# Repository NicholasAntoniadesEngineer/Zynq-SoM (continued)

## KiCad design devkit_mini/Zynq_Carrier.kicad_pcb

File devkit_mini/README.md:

<!-- schgen:gallery -->
<!-- GENERATED by `schgen gallery` — edits between these markers are overwritten -->
## Generated 3D board views

The placed board rendered from 8 angles by `schgen board` (kicad-cli, the real component 3D models) — regenerated and committed every build, just like the sheets below.

|   |   |   |   |
|---|---|---|---|
| <br>**Perspective (front)** | <br>**Perspective (rear)** | <br>**Top** | <br>**Bottom** |
| <br>**Front edge** | <br>**Back edge** | <br>**Left edge** | <br>**Right edge** |

## Ratsnest views

Placed-board airwires, regenerated by `schgen board`: blue/orange = the subsystem's parts (top/bottom side), steel = SoM, green = intra-subsystem, red = to the SoM. `wired` = in `placement.wired_sheets`.

|   |   |
|---|---|
| <br>**Board (top)** | <br>**Board (bottom)** |
| <br>**SoM region** |   |

|   |   |   |   |
|---|---|---|---|
| <br>**debug_boot** | <br>**mechanical** | <br>**pd_input** `wired` | <br>**power** `wired` |
| <br>**power_mon** | <br>**power_som** | <br>**uart_bridge** `wired` | <br>**usb_uart_connector** `wired` |

## Generated schematics

Block diagram and all 12 devkit_mini sheets, regenerated by `schgen board` —
every PNG below passed the netlist, ERC and visual gates.

|   |   |   |
|---|---|---|
| <br>**debug_boot** | <br>**mechanical** | <br>**pd_input** |
| <br>**power** | <br>**power_mon** | <br>**power_som** |
| <br>**som_decoupling** | <br>**som_j1** | <br>**som_j2** |
| <br>**som_j3** | <br>**uart_bridge** | <br>**usb_uart_connector** |

| sheet | description |
|---|---|
| [debug_boot](renders/debug_boot.png) | JTAG + SWD headers, boot-request DIP, reset |
| [mechanical](renders/mechanical.png) | Mechanical: M3 mounts + chassis-GND bond (fiducials are PCB-only, emitted by the placer) |
| [pd_input](renders/pd_input.png) | Power inlet: USB-C PD 20V/3A + TPS26631 eFuse |
| [power](renders/power.png) | Power: +VIN->+5V->+3V3 bucks + +1V8 LDO, PG LEDs |
| [power_mon](renders/power_mon.png) | Rail telemetry: 2x INA3221 + shunts (I2C 0x40/41) |
| [power_som](renders/power_som.png) | Power: +VIN -> +5V_SOM always-on buck |
| [som_decoupling](renders/som_decoupling.png) | SoM power-entry decoupling under the DF40 mezzanine |
| [som_j1](renders/som_j1.png) | SoM J1: power / USB / STM32 / JTAG / SDIO / ETH MDI |
| [som_j2](renders/som_j2.png) | SoM J2: FPGA bank 13/33 IO + VCCO rails |
| [som_j3](renders/som_j3.png) | SoM J3: FPGA bank 33/34/35 IO + VCCO rails |
| [uart_bridge](renders/uart_bridge.png) | UART bridge: CP2102N USB-UART |
| [usb_uart_connector](renders/usb_uart_connector.png) | USB-C UFP console port -> CP2102N |
<!-- /schgen:gallery -->

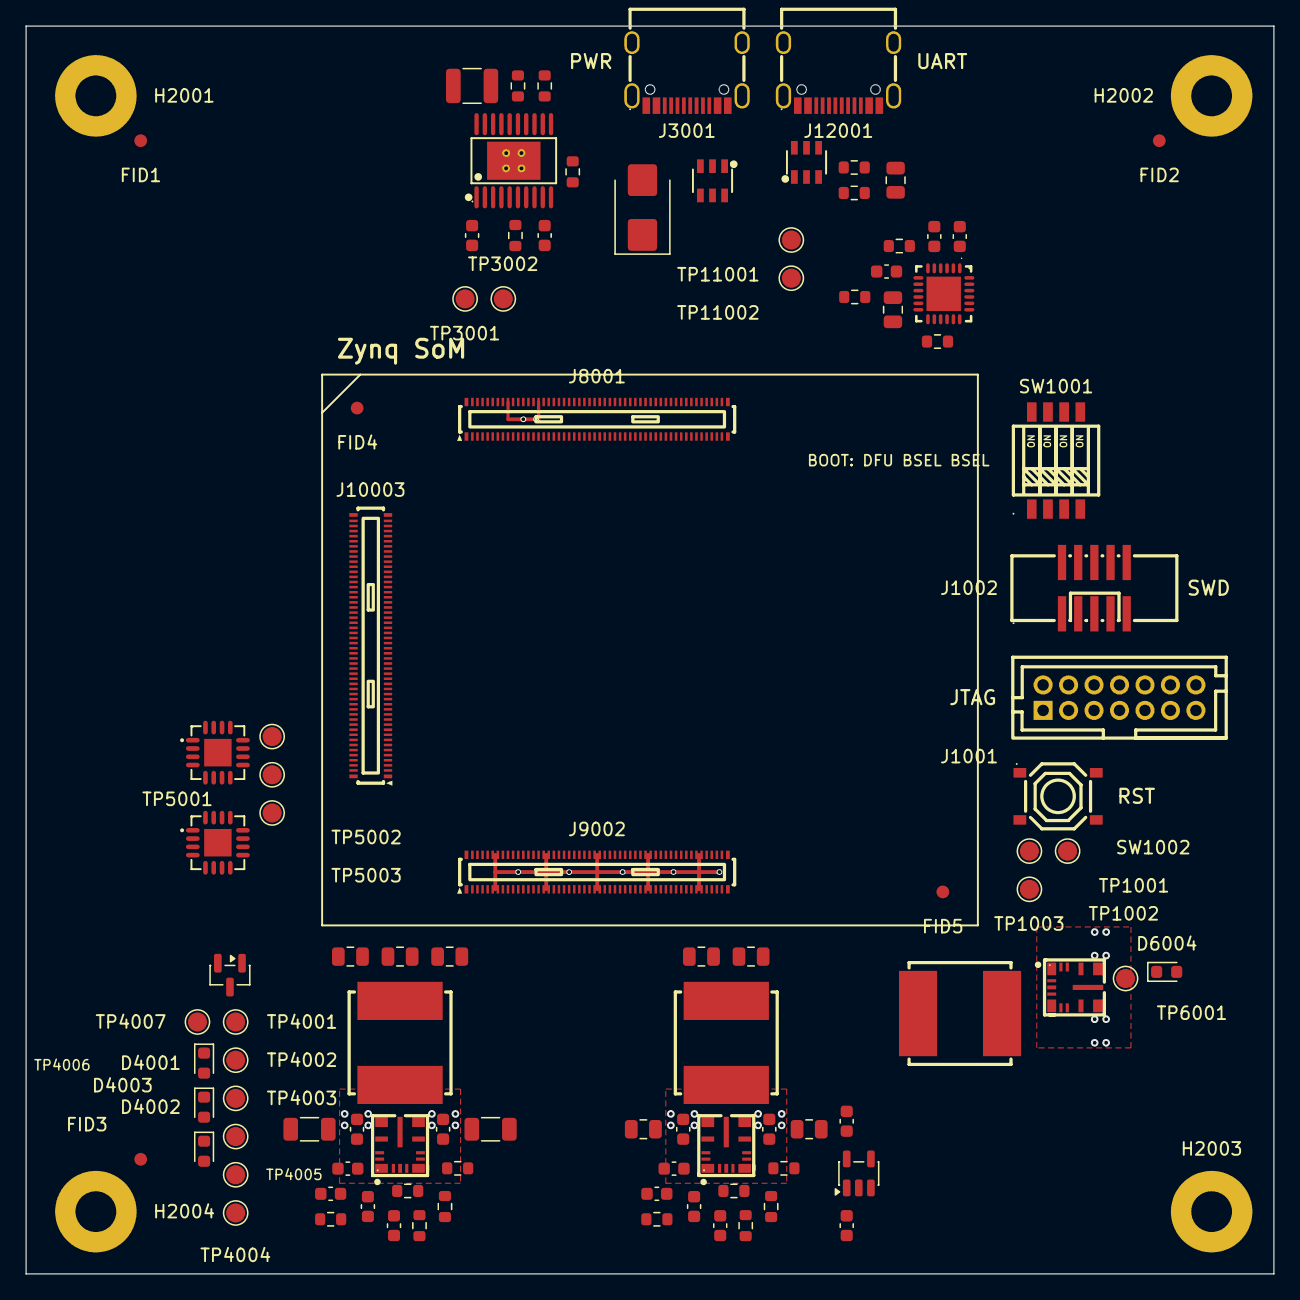
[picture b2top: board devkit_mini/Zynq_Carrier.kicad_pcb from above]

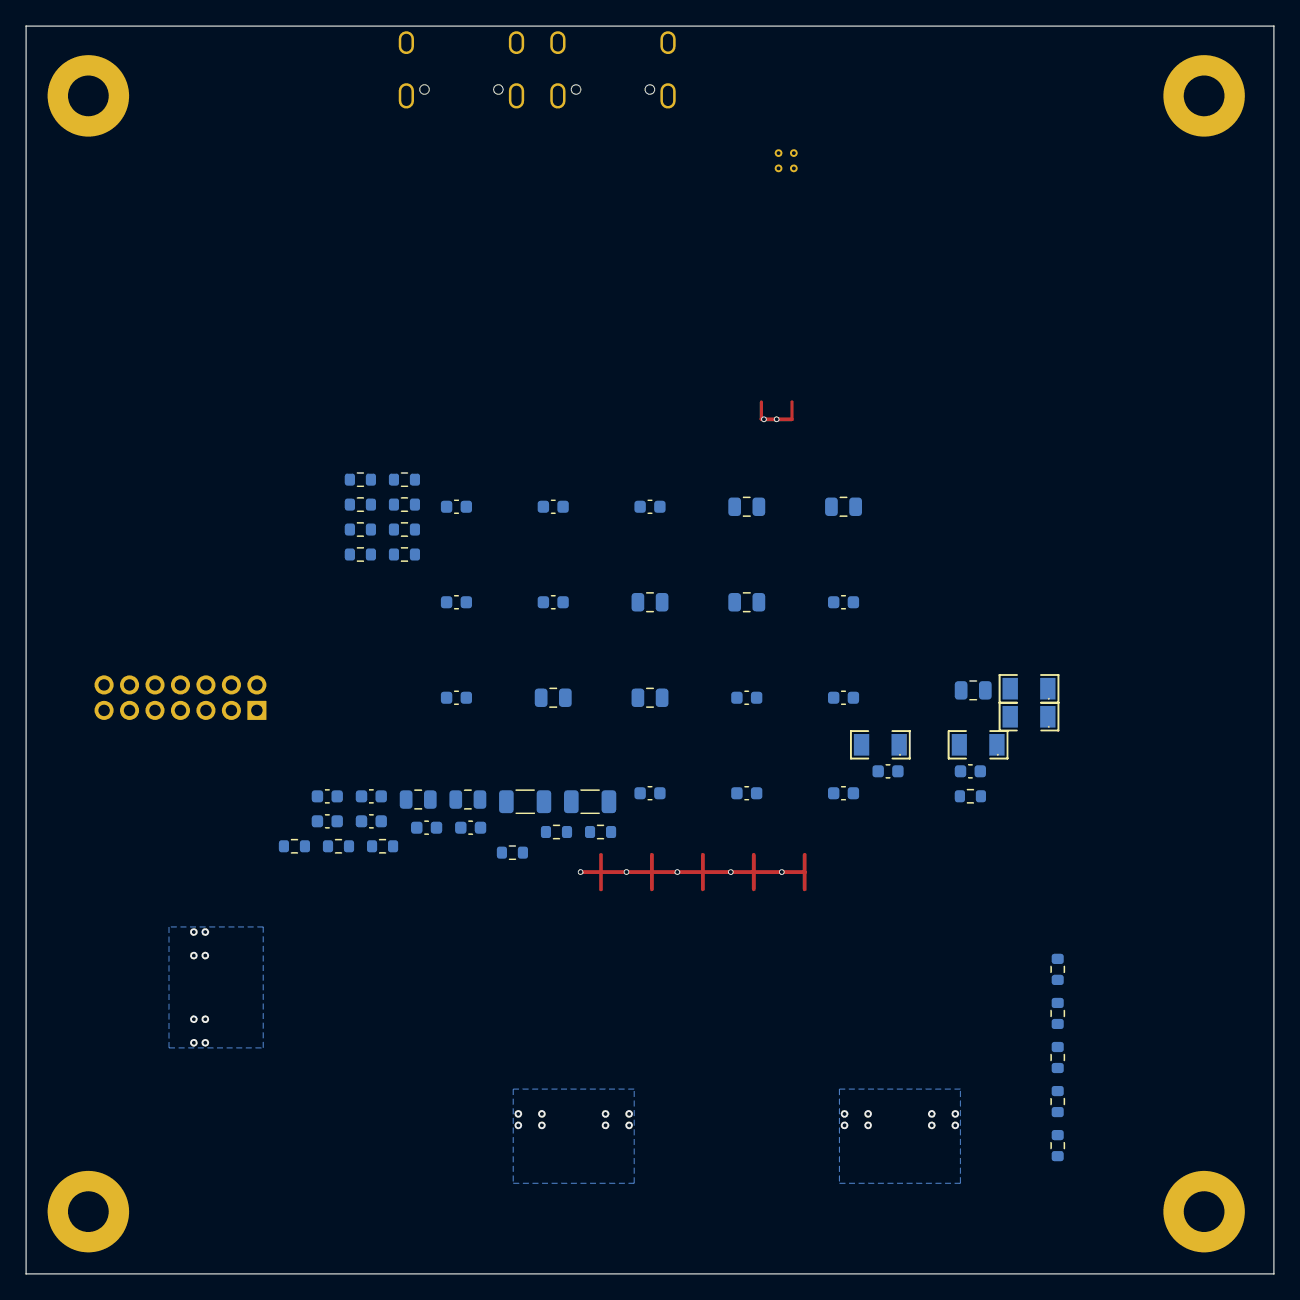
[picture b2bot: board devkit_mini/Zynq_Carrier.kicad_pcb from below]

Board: 4 copper layers, 98.0 x 98.0 mm, 160 parts (55 on the bottom side), 84 nets.

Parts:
C3001, C4001, C4004, C4007, C4009, C4025, C4029, C5001, C5002, C6014, C6017, C6025, C7003, C7004, C7005, C7006, C7009, C7010, C7011, C7012, C7015, C7016, C7017, C7018, C11001, C11003, C11004: 100n; C_0603_1608Metric
C3002: 10u; C_1210_3225Metric
C3003: 47n; C_0603_1608Metric
C4002, C4003, C6015, C6016: 10u; C_1206_3216Metric
C4005, C4006, C4008, C4010, C4011, C4026, C4030, C6018, C6019, C7001, C7002, C7007, C7008, C7013, C7014: 22u; C_0805_2012Metric
C4012, C4013, C4024, C4028, C4031, C4032, C6022, C6023: 1u; C_0603_1608Metric
C4023, C4027, C6021: 22p; C_0603_1608Metric
C5003, C11002, C12001: 10u; C_0805_2012Metric
D3001: SMBJ22A; D_SMB
D4001, D4002, D4003, D6004: red; LED_0603_1608Metric
FID1, FID2, FID3, FID4, FID5: Fiducial; Fiducial_1mm_Mask2mm
H2001, H2002, H2003, H2004: MountingHole_M3; MountingHole_3.2mm_M3_Pad
J1001: 878311420
J1002: HX_JN1.27-2x5; HX_JN1.27-2x5_TP_H4.9
J3001, J12001: TYPE-C-31-M-12
J8001, J9002, J10003: DF40C-100DP-0.4V(51); DF40C-100DP-0.4V_51
L4001, L4002, L6003: 10uH; SWPA8040S100MT
Q4001: AO3400A; SOT-23
R1001, R1002, R1007, R1008: 4k7; R_0603_1608Metric
R1003: 100R; R_0603_1608Metric
R1004, R1005, R1006, R4002, R4005, R5001: 10k; R_0603_1608Metric
R3003, R3006, R4008: 100k; R_0603_1608Metric
R3004: 5.49k; R_0603_1608Metric
R3005, R12001, R12002: 5.1k; R_0603_1608Metric
R4001: 40.2k; R_0603_1608Metric
R4003, R4007, R4012, R4015, R6016, R6019, R11001: 1k; R_0603_1608Metric
R4004: 23.2k; R_0603_1608Metric
R4006, R4009: 330R; R_0603_1608Metric
R4010, R4014, R6018: 22k; R_0603_1608Metric
R4011, R4013, R6017: 10R; R_0603_1608Metric
R6014: 47.5k; R_0603_1608Metric
R6015: 13k; R_0603_1608Metric
R11002: 22k1; R_0603_1608Metric
R11003: 47k5; R_0603_1608Metric
RS5001, RS5002, RS5003: 10mR; RLM12FTCMR010
RS5004: 20mR; RLM12FTCMR020
SW1001: DIP-4; DSHP04TSGER
SW1002: RESET; TS-1187A-B-A-B
TP1001: SDIO_CLK; TestPoint_Pad_D1.5mm
TP1002: SDIO_CMD; TestPoint_Pad_D1.5mm
TP1003: VBUS_OUT_EN; TestPoint_Pad_D1.5mm
TP3001: +VBUS_IN; TestPoint_Pad_D1.5mm
TP3002: +VIN; TestPoint_Pad_D1.5mm
TP4001: +5V; TestPoint_Pad_D1.5mm
TP4002: +3V3; TestPoint_Pad_D1.5mm
TP4003: +1V8; TestPoint_Pad_D1.5mm
TP4004: GND; TestPoint_Pad_D1.5mm
TP4005: EN_5V0; TestPoint_Pad_D1.5mm
TP4006: EN_3V3; TestPoint_Pad_D1.5mm
TP4007: EN_1V8; TestPoint_Pad_D1.5mm
TP5001: +3V3_SC; TestPoint_Pad_D1.5mm
TP5002: STM32_I2C2_SCL; TestPoint_Pad_D1.5mm
TP5003: STM32_I2C2_SDA; TestPoint_Pad_D1.5mm
TP6001: +5V_SOM; TestPoint_Pad_D1.5mm
TP11001: ZYNQ_PS_UART0_TXD; TestPoint_Pad_D1.5mm
TP11002: ZYNQ_PS_UART0_RXD; TestPoint_Pad_D1.5mm
U3001: TPS26631PWPR
U3002, U12001: USBLC6-2SC6
U4001, U4002, U6004: LM61460AANRJRR
U4003: AP2112K-1.8; SOT-23-5
U5001, U5002: INA3221AIRGVR
U11001: CP2102N-A02; CP2102N-A02-GQFN24R

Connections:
+1V8: R4007.1, RS5004.2, TP4003.1, U5002.11
+1V8_REG: C4013.1, RS5004.1, U4003.5, U5002.12
+3V3: C4012.1, C7007.1, C7008.1, C7009.1, C7010.1, C7011.1, C7012.1, C11001.1, C11002.1, C11003.1, C11004.1, D4003.2, J1001.2, J9002.1, J9002.2, J9002.3, J9002.98, J9002.99, J9002.100, J10003.1, J10003.2, J10003.4, J10003.97, J10003.99, R1001.1, R1002.1, R11001.1, RS5003.2, TP4002.1, U4003.1, U5001.1, U11001.5, U11001.6, U11001.7
+3V3_REG: C4010.1, C4011.1, C4023.1, D4002.2, L4002.2, R4004.1, R4013.1, RS5003.1, U5001.2
+3V3_SC: C5001.1, C5002.1, C5003.1, C7013.1, C7014.1, C7015.1, C7016.1, C7017.1, C7018.1, J1002.1, J8001.37, R1003.1, R1004.1, R1005.1, R1006.1, R1007.1, R1008.1, R3006.1, R5001.1, TP5001.1, U3002.5, U5001.4, U5001.16, U5002.4, U5002.5, U5002.16
+5V: C4007.1, C4008.1, C4029.1, C4030.1, RS5002.2, TP4001.1, U4002.8, U4002.12, U5001.14
+5V_REG: C4005.1, C4006.1, C4026.1, C4027.1, D4001.2, L4001.2, R4001.1, R4011.1, RS5002.1, U5001.15
+5V_SOM: C6018.1, C6019.1, C6021.1, C7001.1, C7002.1, C7003.1, C7004.1, C7005.1, C7006.1, D6004.2, J8001.1, J8001.2, J8001.3, J8001.4, J8001.5, J8001.6, J8001.7, J8001.8, J8001.9, J8001.10, J8001.11, J8001.12, J8001.13, J8001.14, L6003.2, R6014.1, R6017.1, TP6001.1
+VBUS_IN: C3001.1, D3001.1, J3001.A4B9, J3001.B4A9, R3003.1, TP3001.1, U3001.1, U3001.2, U3001.3, U3001.6, U3001.7
+VIN: C3002.1, RS5001.1, TP3002.1, U3001.18, U3001.19, U3001.20, U5001.12
+VIN_SYS: C4001.1, C4002.1, C4003.1, C4025.1, C6014.1, C6015.1, C6016.1, C6025.1, RS5001.2, U4001.8, U4001.12, U5001.11, U6004.7, U6004.8, U6004.12
/pd_input/PD_USB_DN_CONN: J3001.A7, J3001.B7, U3002.3
/pd_input/PD_USB_DP_CONN: J3001.A6, J3001.B6, U3002.1
/power/BIAS_3V3: C4032.1, R4013.2, U4002.1
/power/BIAS_5V0: C4028.1, R4011.2, U4001.1
/power/RT_3V3: R4014.1, U4002.6
/power/RT_5V0: R4010.1, U4001.6
/power_som/BIAS_5V_SOM: C6023.1, R6017.2, U6004.1
/power_som/RT_5V_SOM: R6018.1, U6004.6
/uart_bridge/CP2102N_VBUS_SNS: R11002.2, R11003.1, U11001.8
/usb_uart_connector/USB_UART_DM_CONN: J12001.A7, J12001.B7, U12001.3
/usb_uart_connector/USB_UART_DP_CONN: J12001.A6, J12001.B6, U12001.1
CHASSIS_GND: H2001.1, H2002.1, H2003.1, H2004.1, J3001.1, J3001.2, J3001.3, J3001.4, J12001.1, J12001.2, J12001.3, J12001.4
EN_1V8: TP4007.1, U4003.3
EN_3V3: TP4006.1, U4002.7
EN_5V0: TP4005.1, U4001.7
GND: C3001.2, C3002.2, C3003.2, C4001.2, C4002.2, C4003.2, C4005.2, C4006.2, C4007.2, C4008.2, C4010.2, C4011.2, C4012.2, C4013.2, C4024.2, C4025.2, C4026.2, C4028.2, C4029.2, C4030.2, C4031.2, C4032.2, C5001.2, C5002.2, C5003.2, C6014.2, C6015.2, C6016.2, C6018.2, C6019.2, C6022.2, C6023.2, C6025.2, C7001.2, C7002.2, C7003.2, C7004.2, C7005.2, C7006.2, C7007.2, C7008.2, C7009.2, C7010.2, C7011.2, C7012.2, C7013.2, C7014.2, C7015.2, C7016.2, C7017.2, C7018.2, C11001.2, C11002.2, C11003.2, C11004.2, C12001.2, D3001.2, J1001.1, J1001.3, J1001.5, J1001.7, J1001.9, J1001.11, J1001.13, J1002.3, J1002.5, J1002.9, J3001.A1B12, J3001.B1A12, J8001.15, J8001.16, J8001.17, J8001.18, J8001.23, J8001.28, J8001.34, J8001.39, J8001.44, J8001.51, J8001.62, J8001.63, J8001.72, J8001.75, J8001.81, J8001.82, J8001.87, J8001.93, J8001.96, J8001.99, J9002.4, J9002.5, J9002.6, J9002.15, J9002.16, J9002.25, J9002.26, J9002.35, J9002.36, J9002.45, J9002.46, J9002.55, J9002.56, J9002.65, J9002.66, J9002.75, J9002.76, J9002.85, J9002.86, J9002.95, J9002.96, J9002.97, J10003.3, J10003.6, J10003.12, J10003.13, J10003.18, J10003.23, J10003.28, J10003.33, J10003.38, J10003.43, J10003.48, J10003.53, J10003.58, J10003.63, J10003.68, J10003.73, J10003.80, J10003.83, J10003.90, J10003.95, J10003.100, J12001.A1B12, J12001.B1A12, Q4001.2, R3004.2, R3005.2, R4002.2, R4003.2, R4005.2, R4006.2, R4008.2, R4010.2, R4014.2, R6015.2, R6016.2, R6018.2, R11003.2, R12001.2, R12002.2, SW1001.5, SW1001.6, SW1001.7, SW1002.3, SW1002.4, TP4004.1, U3001.9, U3001.12, U3001.16, U3001.21, U3002.2, U4001.3, U4001.9, U4001.11, U4002.3, U4002.9, U4002.11, U4003.2, U5001.3, U5001.5, U5001.17, U5002.1, U5002.2, U5002.3, U5002.14, U5002.15, U5002.17, U6004.3, U6004.9, U6004.11, U11001.2, U11001.25, U12001.2
unnamed: C4023.2, R4015.1
unnamed: C4027.2, R4012.1
unnamed: C6021.2, R6019.1
unnamed: D4001.1, R4003.1
unnamed: D4002.1, R4006.1
unnamed: D4003.1, R4009.1
unnamed: D6004.1, R6016.1
unnamed: J12001.A5, R12001.1
unnamed: J12001.B5, R12002.1
unnamed: Q4001.3, R4009.2
unnamed: Q4001.1, R4007.2, R4008.1
unnamed: R1003.2, SW1001.8
unnamed: R1006.2, SW1001.4
unnamed: R3005.1, U3001.11
unnamed: R3003.2, R3004.1, U3001.8
unnamed: C3003.1, U3001.10
unnamed: C4004.1, U4001.13, U4001.14
unnamed: R4001.2, R4002.1, R4012.2, U4001.4
unnamed: C4004.2, L4001.1, U4001.10
unnamed: C4024.1, U4001.2
unnamed: C4009.1, U4002.13, U4002.14
unnamed: R4004.2, R4005.1, R4015.2, U4002.4
unnamed: C4009.2, L4002.1, U4002.10
unnamed: C4031.1, U4002.2
unnamed: C6017.1, U6004.13, U6004.14
unnamed: R6014.2, R6015.1, R6019.2, U6004.4
unnamed: C6017.2, L6003.1, U6004.10
unnamed: C6022.1, U6004.2
unnamed: R11001.2, U11001.9
PD_FLT_N: R3006.2, U3001.15
PMON_ALERT_N: R5001.2, U5001.9, U5002.9
SDIO_CLK: J8001.67, TP1001.1
SDIO_CMD: J8001.69, TP1002.1
STM32_BOOT0: J8001.57, SW1001.1
STM32_GPIO5: J1002.4, J8001.53
STM32_GPIO6: J1002.2, J8001.45
STM32_GPIO7: J8001.59, R1004.2, SW1001.2
STM32_GPIO8: J8001.54, R1005.2, SW1001.3
STM32_I2C2_SCL: J8001.55, R1007.2, TP5002.1, U5001.6, U5002.6
STM32_I2C2_SDA: J8001.49, R1008.2, TP5003.1, U5001.7, U5002.7
STM32_NRST: J1002.10, J8001.47, SW1002.1, SW1002.2
STM32_USB_CC1: J3001.A5, J8001.29
STM32_USB_CC2: J3001.B5, J8001.31
STM32_USB_D_N: J8001.21, U3002.4
STM32_USB_D_P: J8001.19, U3002.6
USB_UART_DM: U11001.4, U12001.4
USB_UART_DP: U11001.3, U12001.6
USB_UART_VBUS: C12001.1, J12001.A4B9, J12001.B4A9, R11002.1, U12001.5
VBUS_OUT_EN: J8001.38, TP1003.1
ZYNQ_PS_UART0_CTS_N: J9002.11, U11001.19
ZYNQ_PS_UART0_RTS_N: J9002.8, U11001.18
ZYNQ_PS_UART0_RXD: J8001.42, TP11002.1, U11001.21
ZYNQ_PS_UART0_TXD: J8001.48, TP11001.1, U11001.20
ZYNQ_TCK: J1001.6, J8001.64
ZYNQ_TDI: J1001.10, J8001.70, R1002.2
ZYNQ_TDO: J1001.8, J8001.68
ZYNQ_TMS: J1001.4, J8001.66, R1001.2

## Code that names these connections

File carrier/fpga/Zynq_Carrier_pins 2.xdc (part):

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##############################################################################

# ---- bank 13 — VCCO = +3V3 (43 pins) --------------------
set_property -dict {PACKAGE_PIN AA9  IOSTANDARD LVCMOS33} [get_ports {DBG_UART_RXD}]  ;# J2.42 IO_L11P_T1_SRCC_13 <- usb_jtag
#   ^ SRCC-capable: # create_clock -name DBG_UART_RXD -period <ns> [get_ports {DBG_UART_RXD}]
set_property -dict {PACKAGE_PIN AA8  IOSTANDARD LVCMOS33} [get_ports {DBG_UART_TXD}]  ;# J2.40 IO_L11N_T1_SRCC_13 <- usb_jtag
set_property -dict {PACKAGE_PIN V10  IOSTANDARD LVCMOS33} [get_ports {ESC_BUF_OE_N}]  ;# J2.57 IO_L1P_T0_13 <- motor_pwm
set_property -dict {PACKAGE_PIN V9   IOSTANDARD LVCMOS33} [get_ports {ESC_FAULT_N}]  ;# J2.37 IO_L1N_T0_13 <- motor_sense
set_property -dict {PACKAGE_PIN U7   IOSTANDARD LVCMOS33} [get_ports {IO_25_13}]  ;# J2.23 IO_25_13 <- user_io
set_property -dict {PACKAGE_PIN Y10  IOSTANDARD LVCMOS33} [get_ports {IO_L10_N_13}]  ;# J2.51 IO_L10N_T1_13 <- pmod
set_property -dict {PACKAGE_PIN Y11  IOSTANDARD LVCMOS33} [get_ports {IO_L10_P_13}]  ;# J2.53 IO_L10P_T1_13 <- pmod
set_property -dict {PACKAGE_PIN AB2  IOSTANDARD LVCMOS33} [get_ports {IO_L15_P_13}]  ;# J2.9 IO_L15P_T2_DQS_13 <- user_io
set_property -dict {PACKAGE_PIN R6   IOSTANDARD LVCMOS33} [get_ports {IO_L19_P_13}]  ;# J2.12 IO_L19P_T3_13 <- user_io
set_property -dict {PACKAGE_PIN V5   IOSTANDARD LVCMOS33} [get_ports {IO_L21_P_13}]  ;# J2.13 IO_L21P_T3_DQS_13 <- user_io
set_property -dict {PACKAGE_PIN U6   IOSTANDARD LVCMOS33} [get_ports {IO_L22_P_13}]  ;# J2.19 IO_L22P_T3_13 <- user_io
set_property -dict {PACKAGE_PIN W5   IOSTANDARD LVCMOS33} [get_ports {IO_L24_N_13}]  ;# J2.7 IO_L24N_T3_13 <- user_io
set_property -dict {PACKAGE_PIN W6   IOSTANDARD LVCMOS33} [get_ports {IO_L24_P_13}]  ;# J2.10 IO_L24P_T3_13 <- user_io
set_property -dict {PACKAGE_PIN W8   IOSTANDARD LVCMOS33} [get_ports {IO_L2_N_13}]  ;# J2.14 IO_L2N_T0_13 <- pmod
set_property -dict {PACKAGE_PIN V8   IOSTANDARD LVCMOS33} [get_ports {IO_L2_P_13}]  ;# J2.20 IO_L2P_T0_13 <- pmod
set_property -dict {PACKAGE_PIN W10  IOSTANDARD LVCMOS33} [get_ports {IO_L3_N_13}]  ;# J2.43 IO_L3N_T0_DQS_13 <- pmod
set_property -dict {PACKAGE_PIN W11  IOSTANDARD LVCMOS33} [get_ports {IO_L3_P_13}]  ;# J2.18 IO_L3P_T0_DQS_13 <- pmod
set_property -dict {PACKAGE_PIN W12  IOSTANDARD LVCMOS33} [get_ports {IO_L4_N_13}]  ;# J2.63 IO_L4N_T0_13 <- pmod
set_property -dict {PACKAGE_PIN V12  IOSTANDARD LVCMOS33} [get_ports {IO_L4_P_13}]  ;# J2.61 IO_L4P_T0_13 <- pmod
set_property -dict {PACKAGE_PIN U12  IOSTANDARD LVCMOS33} [get_ports {IO_L5P_13}]  ;# J2.38 IO_L5P_T0_13 <- pmod
set_property -dict {PACKAGE_PIN U11  IOSTANDARD LVCMOS33} [get_ports {IO_L5_N_13}]  ;# J2.24 IO_L5N_T0_13 <- pmod
set_property -dict {PACKAGE_PIN U10  IOSTANDARD LVCMOS33} [get_ports {IO_L6_P_13}]  ;# J2.21 IO_L6P_T0_13 <- user_io
set_property -dict {PACKAGE_PIN AB12 IOSTANDARD LVCMOS33} [get_ports {IO_L7_N_13}]  ;# J2.64 IO_L7N_T1_13 <- pmod
set_property -dict {PACKAGE_PIN AA12 IOSTANDARD LVCMOS33} [get_ports {IO_L7_P_13}]  ;# J2.62 IO_L7P_T1_13 <- pmod
set_property -dict {PACKAGE_PIN AB11 IOSTANDARD LVCMOS33} [get_ports {IO_L8_N_13}]  ;# J2.60 IO_L8N_T1_13 <- pmod
set_property -dict {PACKAGE_PIN AA11 IOSTANDARD LVCMOS33} [get_ports {IO_L8_P_13}]  ;# J2.58 IO_L8P_T1_13 <- pmod
set_property -dict {PACKAGE_PIN AB9  IOSTANDARD LVCMOS33} [get_ports {IO_L9_DQS_N_13}]  ;# J2.48 IO_L9N_T1_DQS_13 <- pmod
set_property -dict {PACKAGE_PIN AB10 IOSTANDARD LVCMOS33} [get_ports {IO_L9_DQS_P_13}]  ;# J2.50 IO_L9P_T1_DQS_13 <- pmod
set_property -dict {PACKAGE_PIN AB6  IOSTANDARD LVCMOS33} [get_ports {LCD_CTP_INT}]  ;# J2.32 IO_L17N_T2_13 <- lcd
set_property -dict {PACKAGE_PIN AB7  IOSTANDARD LVCMOS33} [get_ports {LCD_CTP_RST}]  ;# J2.34 IO_L17P_T2_13 <- lcd
set_property -dict {PACKAGE_PIN AB4  IOSTANDARD LVCMOS33} [get_ports {LCD_CTP_SCL}]  ;# J2.28 IO_L16N_T2_13 <- lcd
set_property -dict {PACKAGE_PIN AB5  IOSTANDARD LVCMOS33} [get_ports {LCD_CTP_SDA}]  ;# J2.30 IO_L16P_T2_13 <- lcd
set_property -dict {PACKAGE_PIN Y6   IOSTANDARD LVCMOS33} [get_ports {PMODX_IO1}]  ;# J2.29 IO_L13P_T2_MRCC_13 <- pmod_expansion
#   ^ MRCC-capable: # create_clock -name PMODX_IO1 -period <ns> [get_ports {PMODX_IO1}]
set_property -dict {PACKAGE_PIN Y5   IOSTANDARD LVCMOS33} [get_ports {PMODX_IO2}]  ;# J2.27 IO_L13N_T2_MRCC_13 <- pmod_expansion
set_property -dict {PACKAGE_PIN V7   IOSTANDARD LVCMOS33} [get_ports {PMODX_IO3}]  ;# J2.33 IO_L23P_T3_13 <- pmod_expansion
set_property -dict {PACKAGE_PIN W7   IOSTANDARD LVCMOS33} [get_ports {PMODX_IO4}]  ;# J2.31 IO_L23N_T3_13 <- pmod_expansion
set_property -dict {PACKAGE_PIN AA7  IOSTANDARD LVCMOS33} [get_ports {PMODX_IO5}]  ;# J2.41 IO_L14P_T2_SRCC_13 <- pmod_expansion
#   ^ SRCC-capable: # create_clock -name PMODX_IO5 -period <ns> [get_ports {PMODX_IO5}]
set_property -dict {PACKAGE_PIN AA6  IOSTANDARD LVCMOS33} [get_ports {PMODX_IO6}]  ;# J2.39 IO_L14N_T2_SRCC_13 <- pmod_expansion
set_property -dict {PACKAGE_PIN Y9   IOSTANDARD LVCMOS33} [get_ports {PMODX_IO7}]  ;# J2.49 IO_L12P_T1_MRCC_13 <- pmod_expansion
#   ^ MRCC-capable: # create_clock -name PMODX_IO7 -period <ns> [get_ports {PMODX_IO7}]
set_property -dict {PACKAGE_PIN Y8   IOSTANDARD LVCMOS33} [get_ports {PMODX_IO8}]  ;# J2.47 IO_L12N_T1_MRCC_13 <- pmod_expansion
set_property -dict {PACKAGE_PIN U9   IOSTANDARD LVCMOS33} [get_ports {SD_CARD_DETECT}]  ;# J2.17 IO_L6N_T0_VREF_13 <- microsd
set_property -dict {PACKAGE_PIN Y4   IOSTANDARD LVCMOS33} [get_ports {ZYNQ_PS_UART0_CTS_N}]  ;# J2.11 IO_L18P_T2_13 <- uart_bridge
set_property -dict {PACKAGE_PIN AA4  IOSTANDARD LVCMOS33} [get_ports {ZYNQ_PS_UART0_RTS_N}]  ;# J2.8 IO_L18N_T2_13 <- uart_bridge

# ---- bank 33 — VCCO = +3V3 (39 pins) --------------------
set_property -dict {PACKAGE_PIN T22  IOSTANDARD LVCMOS33} [get_ports {CAM_EN}]  ;# J3.85 IO_L2P_T0_33 <- camera
set_property -dict {PACKAGE_PIN U22  IOSTANDARD LVCMOS33} [get_ports {CAM_LED}]  ;# J3.87 IO_L2N_T0_33 <- camera
set_property -dict {PACKAGE_PIN T21  IOSTANDARD LVCMOS33} [get_ports {CAM_SCL}]  ;# J3.86 IO_L1P_T0_33 <- camera
set_property -dict {PACKAGE_PIN U21  IOSTANDARD LVCMOS33} [get_ports {CAM_SDA}]  ;# J3.89 IO_L1N_T0_33 <- camera
set_property -dict {PACKAGE_PIN W16  IOSTANDARD LVCMOS33} [get_ports {ESC_PWM_IN0}]  ;# J2.81 IO_L14P_T2_SRCC_33 <- motor_pwm
#   ^ SRCC-capable: # create_clock -name ESC_PWM_IN0 -period <ns> [get_ports {ESC_PWM_IN0}]
set_property -dict {PACKAGE_PIN Y16  IOSTANDARD LVCMOS33} [get_ports {ESC_PWM_IN1}]  ;# J2.83 IO_L14N_T2_SRCC_33 <- motor_pwm
set_property -dict {PACKAGE_PIN Y19  IOSTANDARD LVCMOS33} [get_ports {ESC_PWM_IN2}]  ;# J2.93 IO_L11P_T1_SRCC_33 <- motor_pwm
#   ^ SRCC-capable: # create_clock -name ESC_PWM_IN2 -period <ns> [get_ports {ESC_PWM_IN2}]
set_property -dict {PACKAGE_PIN AA19 IOSTANDARD LVCMOS33} [get_ports {ESC_PWM_IN3}]  ;# J2.91 IO_L11N_T1_SRCC_33 <- motor_pwm
set_property -dict {PACKAGE_PIN V22  IOSTANDARD LVCMOS33} [get_ports {ESC_PWM_IN4}]  ;# J3.91 IO_L3P_T0_DQS_33 <- motor_pwm
set_property -dict {PACKAGE_PIN W22  IOSTANDARD LVCMOS33} [get_ports {ESC_PWM_IN5}]  ;# J3.93 IO_L3N_T0_DQS_33 <- motor_pwm
set_property -dict {PACKAGE_PIN U20  IOSTANDARD LVCMOS33} [get_ports {ESC_PWM_IN6}]  ;# J3.92 IO_L5P_T0_33 <- motor_pwm
set_property -dict {PACKAGE_PIN V20  IOSTANDARD LVCMOS33} [get_ports {ESC_PWM_IN7}]  ;# J3.94 IO_L5N_T0_33 <- motor_pwm
set_property -dict {PACKAGE_PIN W13  IOSTANDARD LVCMOS33} [get_ports {HDMI_RX_5V_DET}]  ;# J2.44 IO_L20N_T3_33 <- hdmi_rx
set_property -dict {PACKAGE_PIN V13  IOSTANDARD LVCMOS33} [get_ports {HDMI_RX_CEC}]  ;# J2.59 IO_L20P_T3_33 <- hdmi_rx
# tmds_pair (100R): HDMI_RX_CLK_P / HDMI_RX_CLK_N
set_property -dict {PACKAGE_PIN Y18  IOSTANDARD TMDS_33} [get_ports {HDMI_RX_CLK_P}]  ;# J2.90 IO_L12P_T1_MRCC_33 <- hdmi_rx, hdmi_rx_term
#   ^ MRCC-capable: # create_clock -name HDMI_RX_CLK_P -period <ns> [get_ports {HDMI_RX_CLK_P}]
set_property -dict {PACKAGE_PIN AA18 IOSTANDARD TMDS_33} [get_ports {HDMI_RX_CLK_N}]  ;# J2.88 IO_L12N_T1_MRCC_33 <- hdmi_rx, hdmi_rx_term
# tmds_pair (100R): HDMI_RX_D0_P / HDMI_RX_D0_N
set_property -dict {PACKAGE_PIN AB19 IOSTANDARD TMDS_33} [get_ports {HDMI_RX_D0_P}]  ;# J2.92 IO_L10P_T1_33 <- hdmi_rx, hdmi_rx_term
set_property -dict {PACKAGE_PIN AB20 IOSTANDARD TMDS_33} [get_ports {HDMI_RX_D0_N}]  ;# J2.94 IO_L10N_T1_33 <- hdmi_rx, hdmi_rx_term
# tmds_pair (100R): HDMI_RX_D1_P / HDMI_RX_D1_N
set_property -dict {PACKAGE_PIN AA17 IOSTANDARD TMDS_33} [get_ports {HDMI_RX_D1_P}]  ;# J2.82 IO_L17P_T2_33 <- hdmi_rx, hdmi_rx_term
set_property -dict {PACKAGE_PIN AB17 IOSTANDARD TMDS_33} [get_ports {HDMI_RX_D1_N}]  ;# J2.84 IO_L17N_T2_33 <- hdmi_rx, hdmi_rx_term
# tmds_pair (100R): HDMI_RX_D2_P / HDMI_RX_D2_N
set_property -dict {PACKAGE_PIN AA16 IOSTANDARD TMDS_33} [get_ports {HDMI_RX_D2_P}]  ;# J2.78 IO_L18P_T2_33 <- hdmi_rx, hdmi_rx_term
set_property -dict {PACKAGE_PIN AB16 IOSTANDARD TMDS_33} [get_ports {HDMI_RX_D2_N}]  ;# J2.80 IO_L18N_T2_33 <- hdmi_rx, hdmi_rx_term
set_property -dict {PACKAGE_PIN V18  IOSTANDARD LVCMOS33} [get_ports {IO_L6_P_33}]  ;# J2.89 IO_L6P_T0_33 <- unclaimed (wave-3 function map)
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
